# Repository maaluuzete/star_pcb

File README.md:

# LED Star Chaser

This is a small and fun electronics project:  
a star-shaped LED chaser built using a classic NE555 timer and two CD4017 decade counters.
The idea was to mix simple logic, old-school components, and a creative PCB shape into something that’s both educational and nice to look at. It’s not meant to be complicated, just satisfying to build and fun to watch!.

## How it works

### NE555 Timer (Astable Oscillator)

The NE555 is configured as an astable oscillator, meaning it continuously generates a square wave.
- The frequency is set by:
  - R1 (1 kΩ);
  - RV1 (50 kΩ potentiometer);
  - C1/C2 (timing capacitors).
    
By turning the potentiometer, you can make the LEDs chase faster or slower. The output of the 555 goes directly to the clock inputs of the CD4017s.

### CD4017 Decade Counters

Two **CD4017** ICs handle the LED sequencing.
- Each 4017 turns on one output at a time (Q0->Q9);
- Each output drives one LED;
- After the last LED, the sequence resets and starts again.
This creates the classic running-light!

---
## Project Preview

---
## Project Structure

```
star_pcb/
├── images/
│ └── star_3d.png
│ └── star_pcb.png
│ └── star_schematic.png
├── kicad/
│ └── gerbers.zip
│ └── starpcb.kicad_pcb
│ └── starpcb.kicad_pro
│ └── starpcb.kicad_sch
├── LICENSE
├── notes.md
└── README.md
```

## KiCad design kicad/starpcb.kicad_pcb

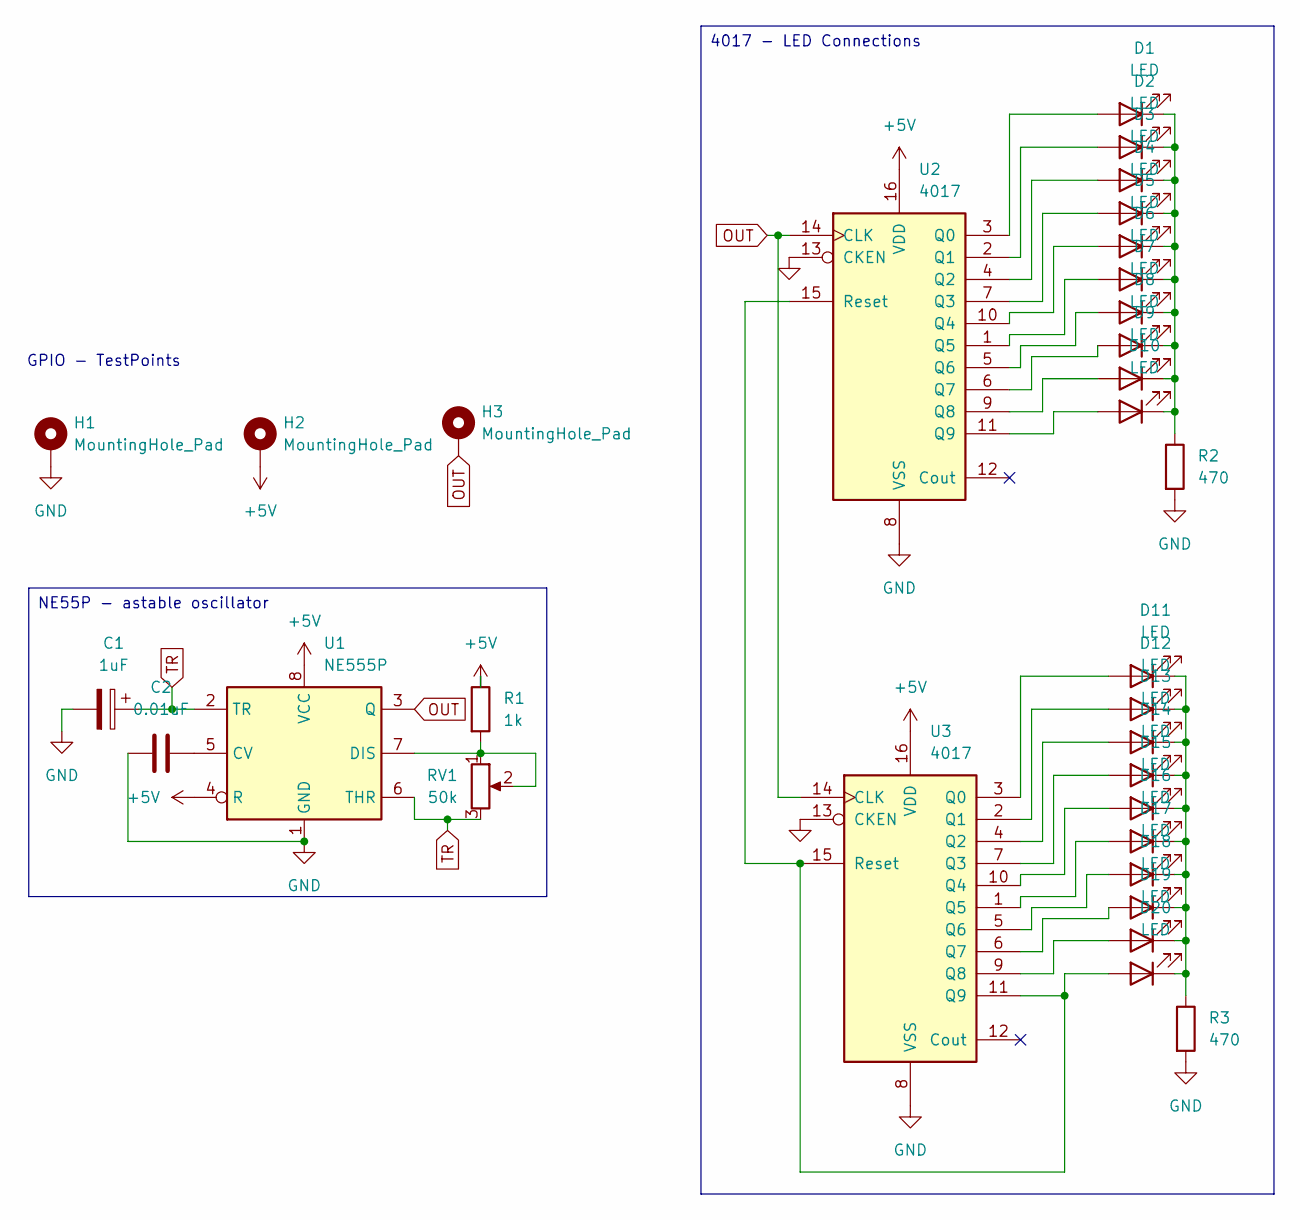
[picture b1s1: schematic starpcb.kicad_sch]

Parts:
C1: 1uF; CP_Radial_D5.0mm_P2.00mm
C2: 0.01uF; CP_Radial_D5.0mm_P2.00mm
D1, D2, D3, D4, D5, D6, D7, D8, D9, D10, D11, D12, D13, D14, D15, D16, D17, D18, D19, D20: LED; LED_D3.0mm
H1, H2, H3: MountingHole_Pad; PinSocket_1x01_P2.54mm_Vertical
R1: 1k; R_Axial_DIN0207_L6.3mm_D2.5mm_P7.62mm_Horizontal
R2, R3: 470; R_Axial_DIN0207_L6.3mm_D2.5mm_P7.62mm_Horizontal
RV1: 50k; R_Axial_DIN0207_L6.3mm_D2.5mm_P7.62mm_Horizontal
U1: NE555P; DIP-8_W7.62mm
U2, U3: 4017; N16

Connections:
+5V: H2.1, R1.1, U1.4 (R), U1.8 (VCC), U2.16 (VDD), U3.16 (VDD)
GND: C1.2, C2.1, H1.1, R2.2, R3.2, U1.1 (GND), U2.8 (VSS), U2.13 (CKEN), U3.8 (VSS), U3.13 (CKEN)
unnamed: D1.2 (A), U2.3 (Q0)
unnamed: D1.1 (K), D2.1 (K), D3.1 (K), D4.1 (K), D5.1 (K), D6.1 (K), D7.1 (K), D8.1 (K), D9.1 (K), D10.1 (K), R2.1
unnamed: D2.2 (A), U2.2 (Q1)
unnamed: D3.2 (A), U2.4 (Q2)
unnamed: D4.2 (A), U2.7 (Q3)
unnamed: D5.2 (A), U2.10 (Q4)
unnamed: D6.2 (A), U2.1 (Q5)
unnamed: D7.2 (A), U2.5 (Q6)
unnamed: D8.2 (A), U2.6 (Q7)
unnamed: D9.2 (A), U2.9 (Q8)
unnamed: D10.2 (A), U2.11 (Q9)
unnamed: D11.2 (A), U3.3 (Q0)
unnamed: D11.1 (K), D12.1 (K), D13.1 (K), D14.1 (K), D15.1 (K), D16.1 (K), D17.1 (K), D18.1 (K), D19.1 (K), D20.1 (K), R3.1
unnamed: D12.2 (A), U3.2 (Q1)
unnamed: D13.2 (A), U3.4 (Q2)
unnamed: D14.2 (A), U3.7 (Q3)
unnamed: D15.2 (A), U3.10 (Q4)
unnamed: D16.2 (A), U3.1 (Q5)
unnamed: D17.2 (A), U3.5 (Q6)
unnamed: D18.2 (A), U3.6 (Q7)
unnamed: D19.2 (A), U3.9 (Q8)
unnamed: D20.2 (A), U2.15 (Reset), U3.11 (Q9), U3.15 (Reset)
unnamed: C2.2, U1.5 (CV)
unnamed: R1.2, RV1.1, RV1.2, U1.7 (DIS)
OUT: H3.1, U1.3 (Q), U2.14 (CLK), U3.14 (CLK)
TR: C1.1, RV1.3, U1.2 (TR), U1.6 (THR)

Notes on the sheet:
4017 - LED Connections
GPIO - TestPoints
NE55P - astable oscillator

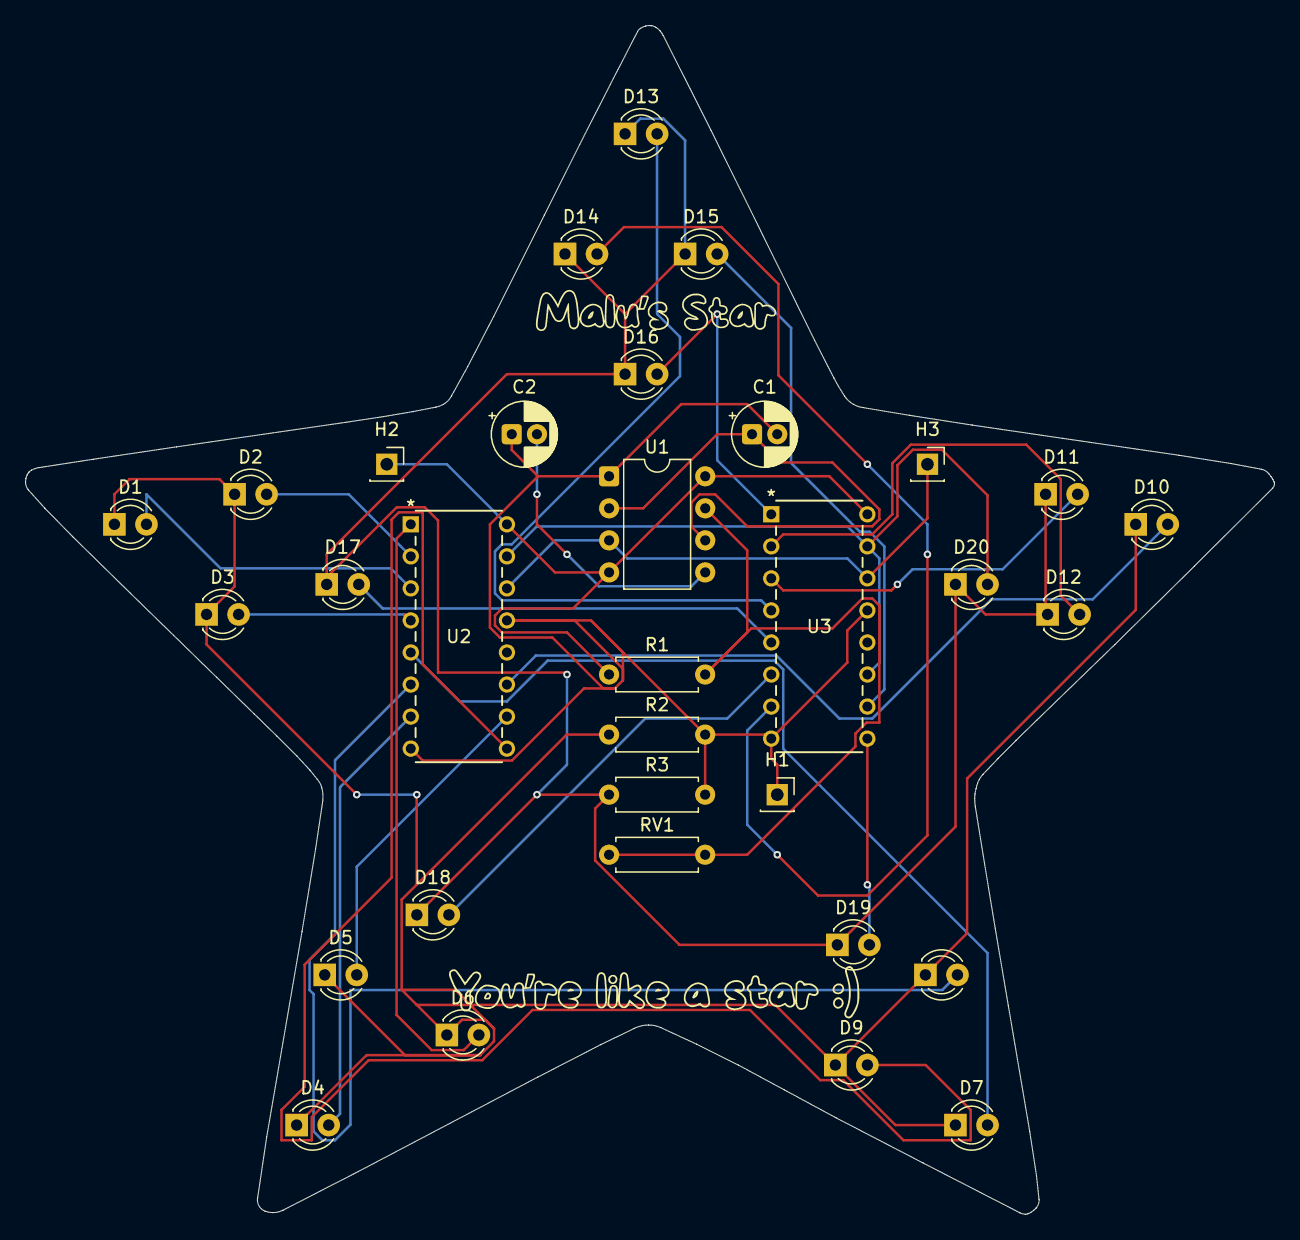
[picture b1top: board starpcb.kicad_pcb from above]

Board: 2 copper layers, 99.0 x 94.2 mm, 32 parts (0 on the bottom side), 28 nets.

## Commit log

2026-01-21 Add initial diary entry for PCB work
2026-01-23 Add entry for January 22, 2026, PCB updates
2026-01-23 Refactor code structure for improved readability and maintainability
2026-01-23 Update README.md for better formatting
    Fix formatting and improve clarity in the README.
2026-01-23 Add explanation for potentiometer adjustment
2026-01-23 Enhance README with project preview and badge
    Added project preview images and EDA badge to README.
